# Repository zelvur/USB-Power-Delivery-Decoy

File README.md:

# USB-Power-Delivery-Decoy-
This is a USB Power Delivery decoy project using RP2040. It requests power from a USB-PD charger and displays the negotiated voltage on a 7-segment display.

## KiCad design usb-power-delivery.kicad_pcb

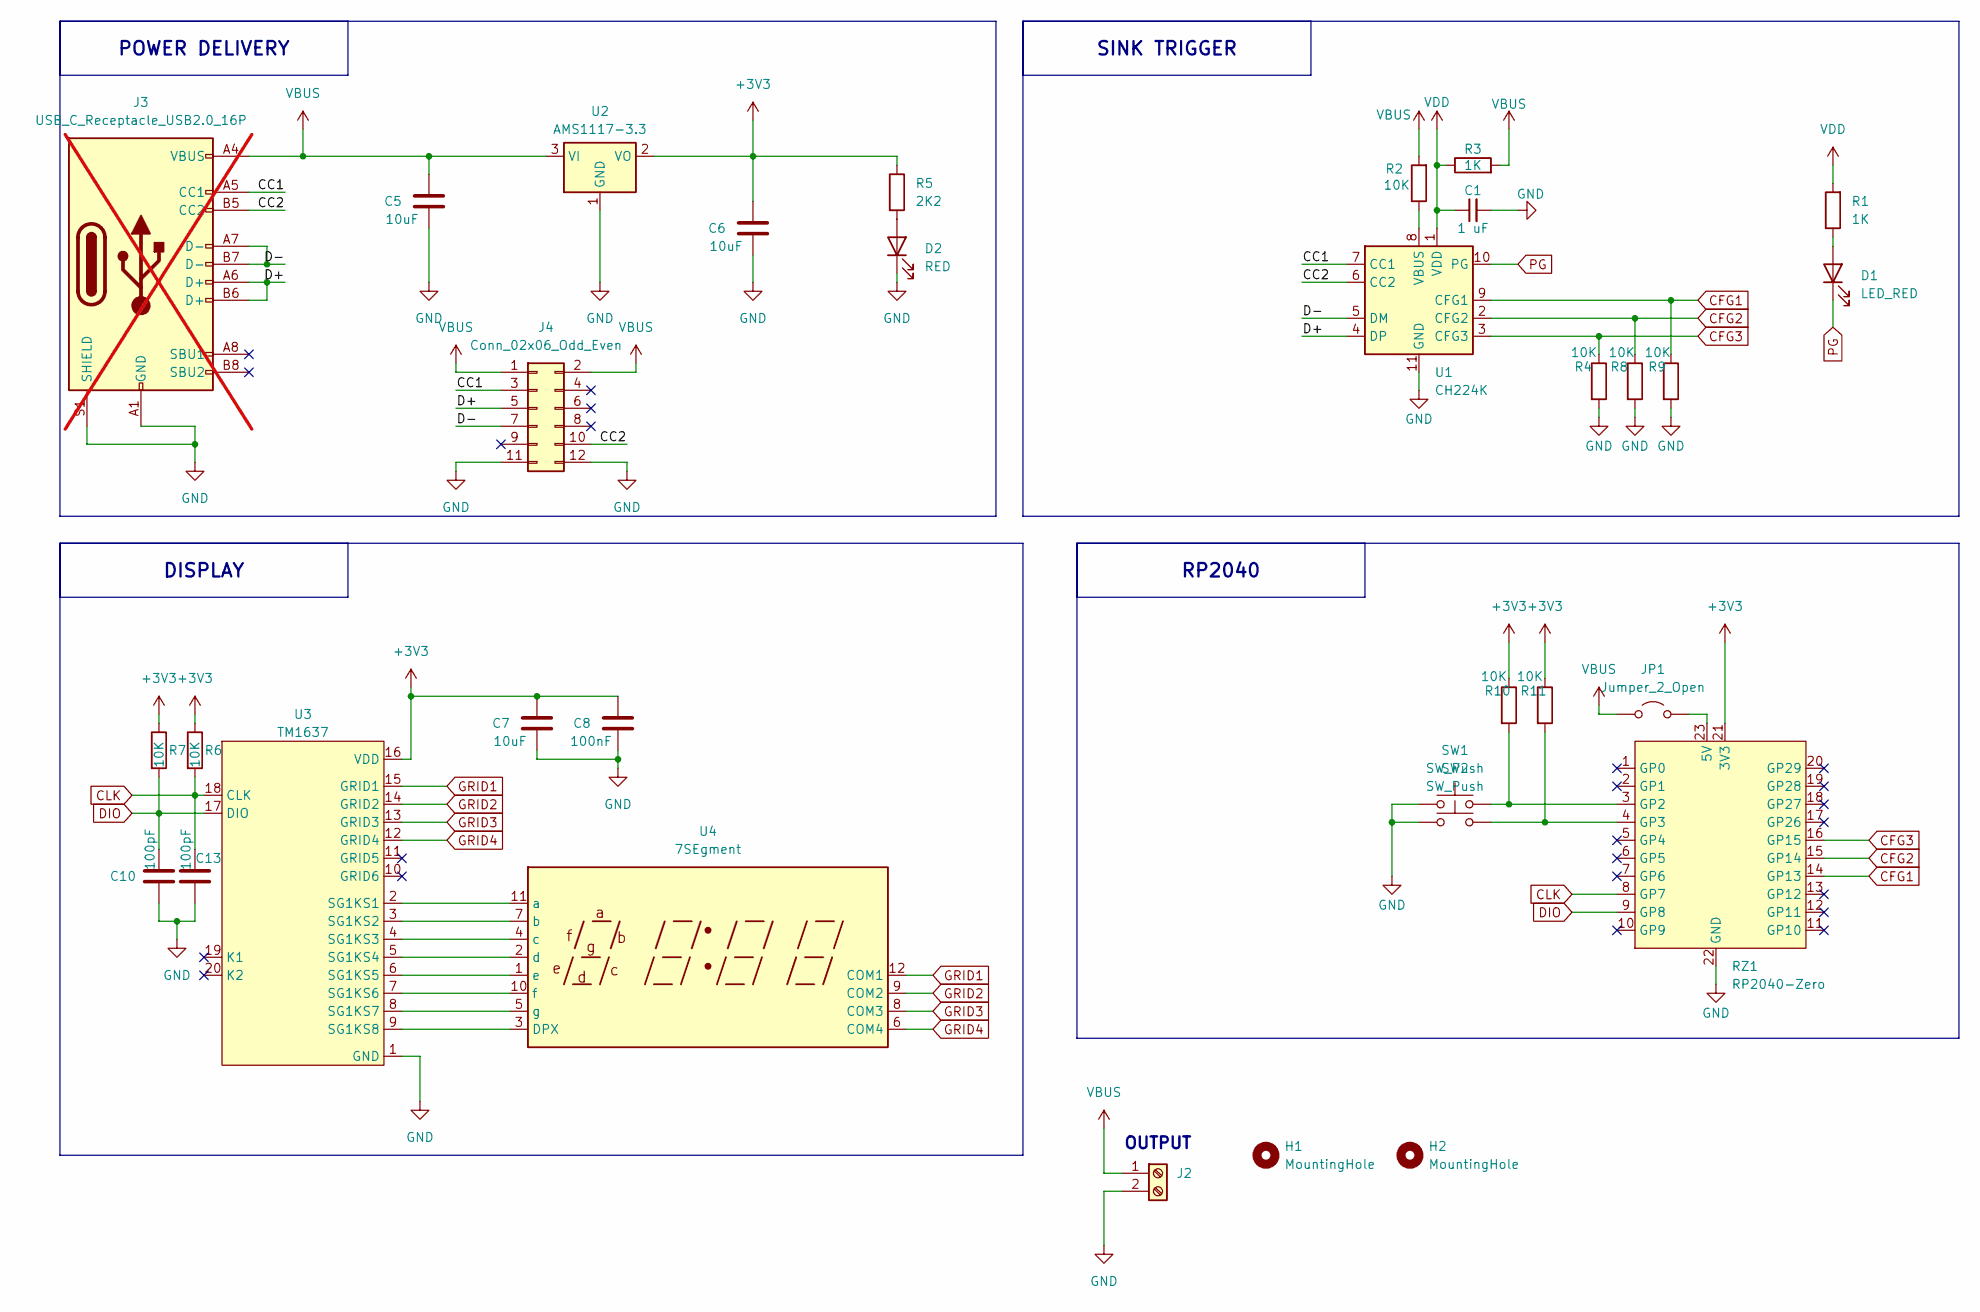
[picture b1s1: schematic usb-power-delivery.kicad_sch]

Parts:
C1: 1 uF; C_0805_2012Metric
C5, C6, C7: 10uF; C_0603_1608Metric
C8: 100nF; C_0603_1608Metric
C10, C13: 100pF; C_0603_1608Metric
D1: LED_RED; LED_0805_2012Metric
D2: RED; LED_0805_2012Metric
H1, H2: MountingHole; MountingHole_3.2mm_M3_Pad_Via
J2: OUTPUT; TerminalBlock_MaiXu_MX126-5.0-02P_1x02_P5.00mm
J3: USB_C_Receptacle_USB2.0_16P; not fitted
J4: Conn_02x06_Odd_Even; PinHeader_2x06_P2.54mm_Vertical
JP1: Jumper_2_Open; SolderJumper-2_P1.3mm_Open_Pad1.0x1.5mm
R1, R3: 1K; R_0805_2012Metric
R2, R4, R8, R9, R10, R11: 10K; R_0805_2012Metric
R5: 2K2; R_0805_2012Metric_Pad1.20x1.40mm_HandSolder
R6, R7: 10K; R_0603_1608Metric
RZ1: RP2040-Zero
SW1, SW2: SW_Push; SW_PUSH_6mm
U1: CH224K; SSOP-10-1EP_3.9x4.9mm_P1mm_EP2.1x3.3mm
U2: AMS1117-3.3; SOT-223-3_TabPin2
U3: TM1637; SOP-20_L12.8-W7.5-P1.27-LS10.4-BL; LCSC Part C5337160
U4: 7SEgment; 7segment_0.36inch_fourinone

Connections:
+3V3: C6.2, C7.2, C8.2, R5.1, R6.1, R7.1, R10.1, R11.1, RZ1.21 (3V3), U2.2 (VO), U3.16 (VDD)
/CC1: J3.A5 (CC1), J4.3, U1.7 (CC1)
/CC2: J3.B5 (CC2), J4.10, U1.6 (CC2)
/D+: J3.A6 (D+), J3.B6 (D+), J4.5, U1.4 (DP)
/D-: J3.A7 (D-), J3.B7 (D-), J4.7, U1.5 (DM)
CFG1: R9.1, RZ1.14 (GP13), U1.9 (CFG1)
CFG2: R8.1, RZ1.15 (GP14), U1.2 (CFG2)
CFG3: R4.1, RZ1.16 (GP15), U1.3 (CFG3)
CLK: C13.2, R6.2, RZ1.8 (GP7), U3.18 (CLK)
DIO: C10.2, R7.2, RZ1.9 (GP8), U3.17 (DIO)
GND: C1.2, C5.1, C6.1, C7.1, C8.1, C10.1, C13.1, D2.1 (K), J2.2, J3.A1 (GND), J3.A12 (GND), J3.B1 (GND), J3.B12 (GND), J3.S1 (SHIELD), J4.11, J4.12, R4.2, R8.2, R9.2, RZ1.22 (GND), SW1.1, SW2.1, U1.11 (GND), U2.1 (GND), U3.1 (GND)
GRID1: U3.15 (GRID1), U4.12 (COM1)
GRID2: U3.14 (GRID2), U4.9 (COM2)
GRID3: U3.13 (GRID3), U4.8 (COM3)
GRID4: U3.12 (GRID4), U4.6 (COM4)
unnamed: D1.2 (A), R1.1
unnamed: D2.2 (A), R5.2
unnamed: JP1.2 (B), RZ1.23 (5V)
unnamed: R10.2, RZ1.3 (GP2), SW1.2
unnamed: R11.2, RZ1.4 (GP3), SW2.2
unnamed: R2.1, U1.8 (VBUS)
unnamed: U3.2 (SG1KS1), U4.11 (a)
unnamed: U3.3 (SG1KS2), U4.7 (b)
unnamed: U3.4 (SG1KS3), U4.4 (c)
unnamed: U3.5 (SG1KS4), U4.2 (d)
unnamed: U3.6 (SG1KS5), U4.1 (e)
unnamed: U3.7 (SG1KS6), U4.10 (f)
unnamed: U3.8 (SG1KS7), U4.5 (g)
unnamed: U3.9 (SG1KS8), U4.3 (DPX)
PG: D1.1 (K), U1.10 (PG)
VBUS: C5.2, J2.1, J3.A4 (VBUS), J3.A9 (VBUS), J3.B4 (VBUS), J3.B9 (VBUS), J4.1, J4.2, JP1.1 (A), R2.2, R3.2, U2.3 (VI)
VDD: C1.1, R1.2, R3.1, U1.1 (VDD)

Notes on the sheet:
OUTPUT
RP2040
DISPLAY
SINK TRIGGER
POWER DELIVERY

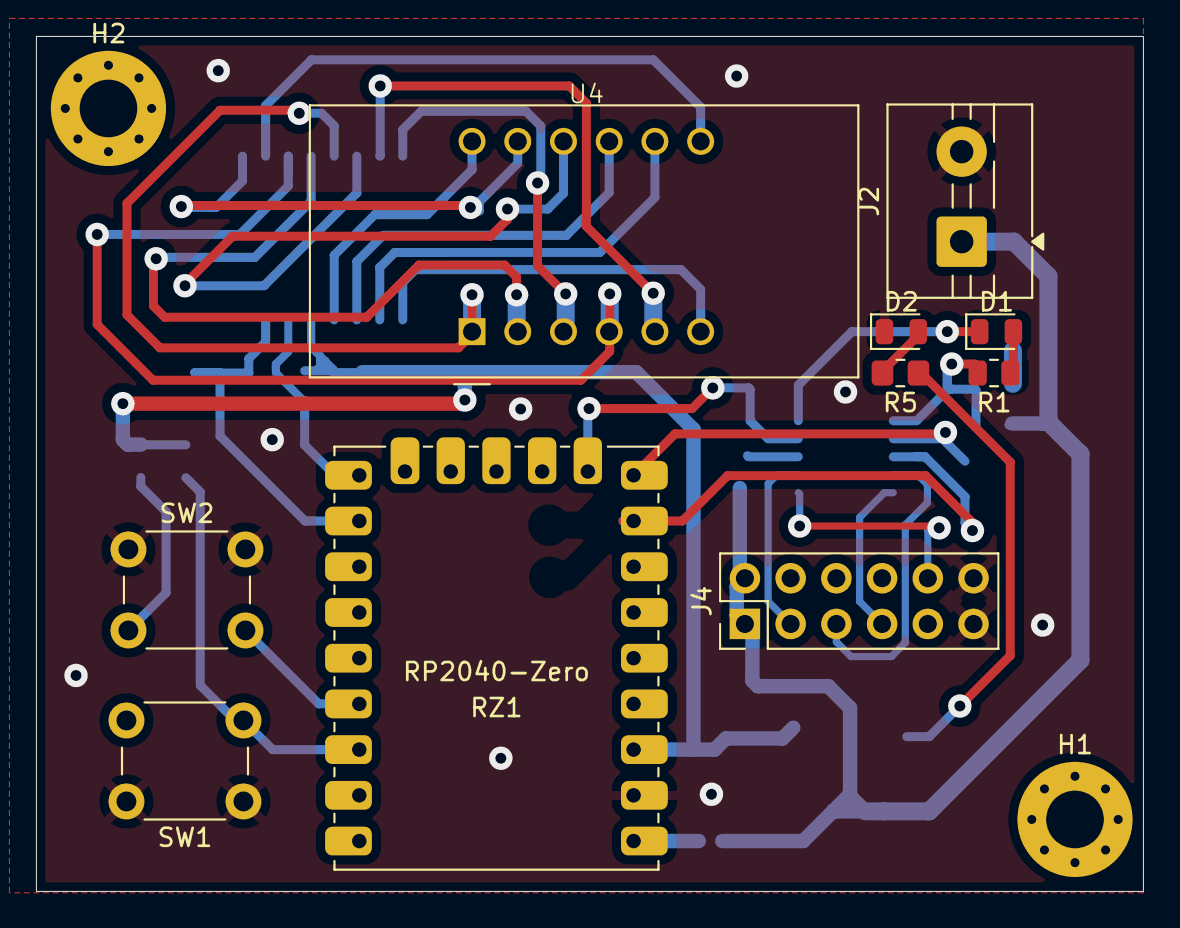
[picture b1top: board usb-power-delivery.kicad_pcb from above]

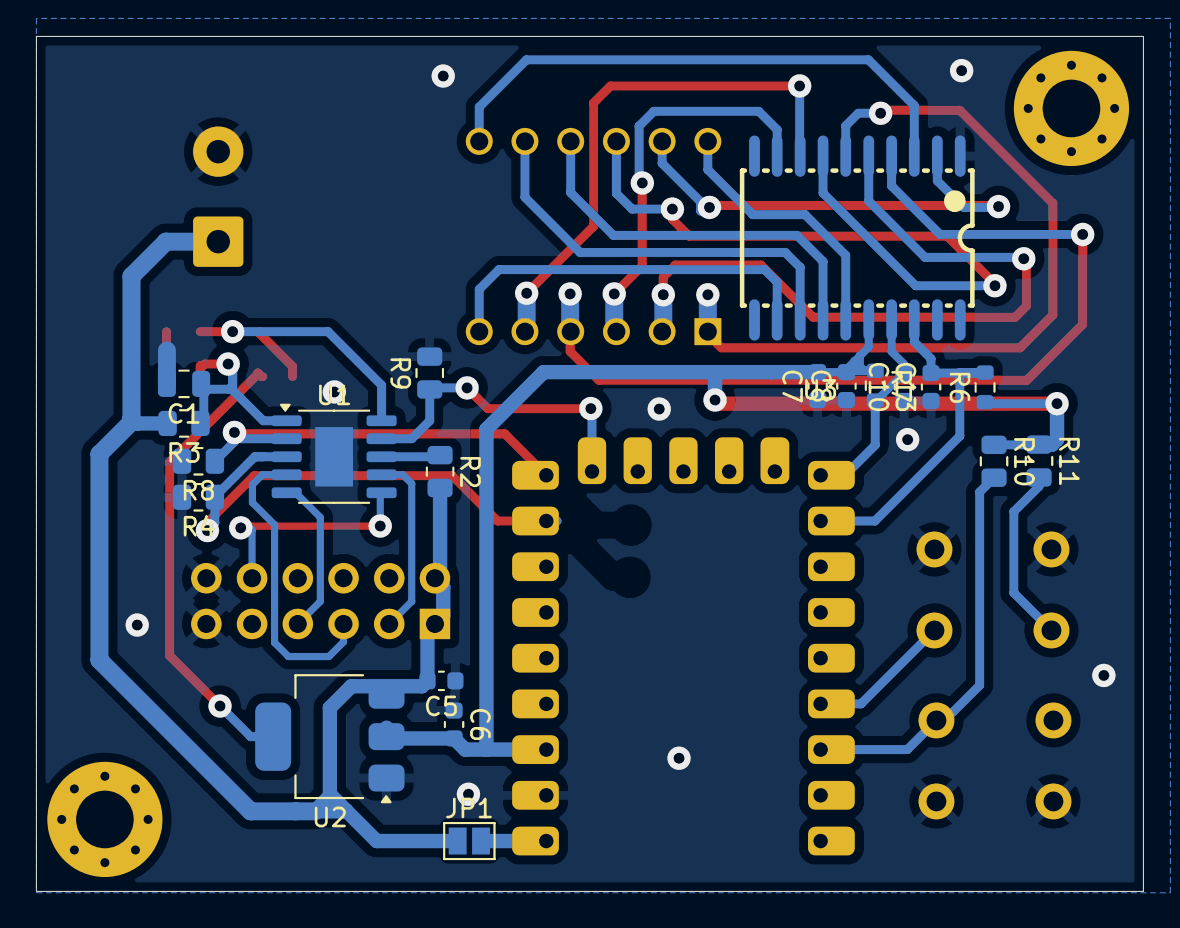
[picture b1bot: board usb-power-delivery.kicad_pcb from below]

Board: 2 copper layers, 61.5 x 47.5 mm, 32 parts (20 on the bottom side), 32 nets.

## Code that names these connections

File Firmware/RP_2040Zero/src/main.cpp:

#include <Arduino.h>

/* ========= PIN CONFIG ========= */
#define BTN_UP     2
#define BTN_DOWN   3

#define CFG1_PIN   13
#define CFG2_PIN   14
#define CFG3_PIN   15

#define TM_CLK     7
#define TM_DIO     8

/* ========= VOLTAGE + CFG TABLE ========= */
const uint8_t cfgTable[][3] = {
  {0,0,0}, // 5V
  {1,1,1}, // 9V
  {1,1,0}, // 12V
  {1,0,0}, // 15V
  {1,0,1}  // 20V
};

const uint8_t voltageTable[] = {5, 9, 12, 15, 20};
uint8_t level = 0;

/* ========= TM1637 DRIVER ========= */
const uint8_t segMap[] = {
  0x3f,0x06,0x5b,0x4f,0x66,
  0x6d,0x7d,0x07,0x7f,0x6f
};

void tmStart() {
  digitalWrite(TM_DIO, HIGH);
  digitalWrite(TM_CLK, HIGH);
  digitalWrite(TM_DIO, LOW);
}

void tmStop() {
  digitalWrite(TM_CLK, LOW);
  digitalWrite(TM_DIO, LOW);
  digitalWrite(TM_CLK, HIGH);
  digitalWrite(TM_DIO, HIGH);
}

void tmWrite(uint8_t data) {
  for (uint8_t i = 0; i < 8; i++) {
    digitalWrite(TM_CLK, LOW);
    digitalWrite(TM_DIO, data & 0x01);
    data >>= 1;
    digitalWrite(TM_CLK, HIGH);
  }
  digitalWrite(TM_CLK, LOW);
  pinMode(TM_DIO, INPUT);
  digitalWrite(TM_CLK, HIGH);
  pinMode(TM_DIO, OUTPUT);
}

void displayVoltage(uint8_t v) {
  uint16_t val = v * 10; // contoh: 5.0 -> 50
  uint8_t d[4] = {
    segMap[(val / 1000) % 10],
    segMap[(val / 100)  % 10],
    segMap[(val / 10)   % 10],
    segMap[val % 10]
  };

  tmStart(); tmWrite(0x40); tmStop();
  tmStart(); tmWrite(0xC0);
  for (uint8_t i = 0; i < 4; i++) tmWrite(d[i]);
  tmStop();
  tmStart(); tmWrite(0x88 | 0x07); tmStop(); // brightness max
}

/* ========= APPLY CFG ========= */
void applyCFG(uint8_t lvl) {
  digitalWrite(CFG1_PIN, cfgTable[lvl][0]);
  digitalWrite(CFG2_PIN, cfgTable[lvl][1]);
  digitalWrite(CFG3_PIN, cfgTable[lvl][2]);
  displayVoltage(voltageTable[lvl]);
}

void setup() {
  pinMode(BTN_UP, INPUT_PULLUP);
  pinMode(BTN_DOWN, INPUT_PULLUP);

  pinMode(CFG1_PIN, OUTPUT);
  pinMode(CFG2_PIN, OUTPUT);
  pinMode(CFG3_PIN, OUTPUT);

  pinMode(TM_CLK, OUTPUT);
  pinMode(TM_DIO, OUTPUT);

  applyCFG(level); // default 5V
}

void loop() {
  static uint32_t t = 0;
  if (millis() - t < 200) return;

  if (!digitalRead(BTN_UP) && level < 4) {
    level++;
    applyCFG(level);
    t = millis();
  }

  if (!digitalRead(BTN_DOWN) && level > 0) {
    level--;
    applyCFG(level);
    t = millis();
  }
}

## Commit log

2026-02-02 Initial Commit
    Schematics - Firmare - Layout
